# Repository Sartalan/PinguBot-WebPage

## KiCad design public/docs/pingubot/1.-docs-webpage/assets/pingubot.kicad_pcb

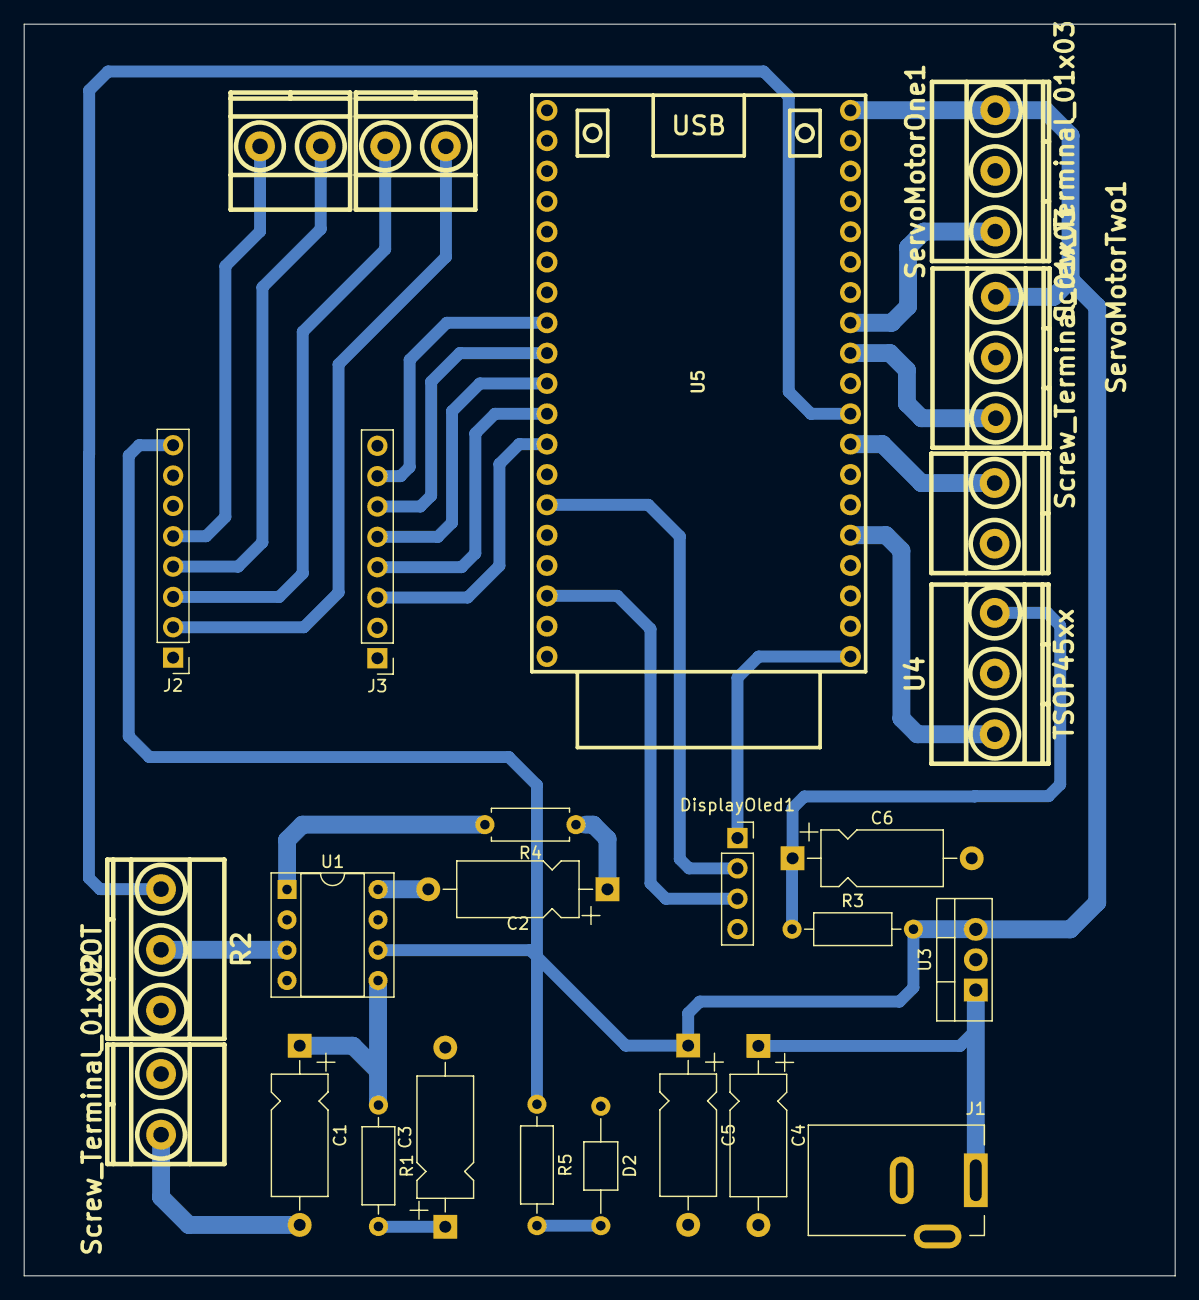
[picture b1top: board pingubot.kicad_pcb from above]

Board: 2 copper layers, 96.3 x 104.8 mm, 26 parts (0 on the bottom side), 29 nets.

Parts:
C1: 220μF; CP_Axial_L10.0mm_D4.5mm_P15.00mm_Horizontal
C2: 10μF; CP_Axial_L10.0mm_D4.5mm_P15.00mm_Horizontal
C3, C6: 0.1yF; CP_Axial_L10.0mm_D4.5mm_P15.00mm_Horizontal
C4, C5: 1μf; CP_Axial_L10.0mm_D4.5mm_P15.00mm_Horizontal
D2: LED; C_Axial_L3.8mm_D2.6mm_P10.00mm_Horizontal
DisplayOled1: Screw_Terminal_01x04; PinSocket_1x04_P2.54mm_Vertical
J1: Jack-DC; BarrelJack_Kycon_KLDX-0202-xC_Horizontal
J2, J3: Conn_01x08_Pin; PinHeader_1x08_P2.54mm_Vertical
Microphone1: Screw_Terminal_01x02; BORNERA2
MotorOne1: Screw_Terminal_01x02; BORNERA2
MotorTwo1: Screw_Terminal_01x02; BORNERA2
R1: 10; R_Axial_DIN0207_L6.3mm_D2.5mm_P10.16mm_Horizontal
R2: POT; BORNERA3
R3: 100; R_Axial_DIN0207_L6.3mm_D2.5mm_P10.16mm_Horizontal
R4: 1,2K; R_Axial_DIN0207_L6.3mm_D2.5mm_P7.62mm_Horizontal
R5: 220; R_Axial_DIN0207_L6.3mm_D2.5mm_P10.16mm_Horizontal
ServoMotorOne1: Screw_Terminal_01x03; BORNERA3
ServoMotorTwo1: Screw_Terminal_01x03; BORNERA3
Speaker1: Screw_Terminal_01x02; BORNERA2
U1: LM386; DIP-8_W7.62mm_Socket
U3: LM7805_TO220; TO-220-3_Vertical
U4: TSOP45xx; BORNERA3
U5: ESP32_DEVKITC

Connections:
3.3V: DisplayOled1.1, U5.1 (3V3)
5V: C5.1, J2.8, R3.2, R5.1, ServoMotorOne1.3, ServoMotorTwo1.3, U1.6 (V+), U3.3 (VO), U5.19 (5V)
GND: C3.2, C4.2, C5.2, C6.2, D2.1 (K), DisplayOled1.4, J1.2, J2.1, J2.6, J3.1, Microphone1.1, R2.3, ServoMotorOne1.2, ServoMotorTwo1.2, Speaker1.1, U1.2 (-), U1.4 (GND), U3.2 (GND), U4.2 (GND), U5.38 (GND)
IR_DATA: U4.1 (OUT), U5.5 (IO34)
MA1: J3.6, U5.28 (IO17)
MA2: J3.7, U5.27 (IO16)
MB1: J3.4, U5.30 (IO18)
MB2: J3.3, U5.31 (IO19)
MO1: J2.5, MotorOne1.2
MO2: J2.4, MotorOne1.1
MO3: J2.3, MotorTwo1.2
MO4: J2.2, MotorTwo1.1
Microphone ADC: Microphone1.2, U5.8 (IO33)
unnamed: C1.1, R1.1, U1.5
unnamed: C2.1, R4.1
unnamed: C2.2, U1.8 (GAIN)
unnamed: C3.1, R1.2
unnamed: D2.2 (A), R5.2
unnamed: R4.2, U1.1 (GAIN)
unnamed: C1.2, Speaker1.2
unnamed: R2.2, U1.3 (+)
unnamed: C6.1, R3.1, U4.3 (Vs)
SCL_DISPLAY: DisplayOled1.3, U5.36 (IO22)
SDA_DISPLAY: DisplayOled1.2, U5.33 (IO21)
STBY: J3.5, U5.29 (IO5)
S_Motor_OUT_1: ServoMotorTwo1.1, U5.11 (IO27)
S_Motor_OUT_2: ServoMotorOne1.1, U5.12 (IO14)
Speaker DAC: R2.1, U5.9 (IO25)
VIN: C4.1, J1.1, U3.1 (VI)

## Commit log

2025-02-12 Initial commit from Astro
2025-02-13 First Viewport Estructure Finished.
2025-02-20 Home Component Improvement
2025-02-20 Nav Improvement
2025-02-20 Footer Improvement
2025-02-20 Nav Icons Added | Nav Component Improved
2025-02-21 Responsive Nav
2025-02-21 Refactor almost all the code from the Nav | pls
2025-02-21 Code Refactored yay
2025-03-01 KiCanvas Api Added
2025-03-01 Nav | Bug Fixed
2025-03-01 View Transition Added
2025-03-02 Dinamic Path's Added
2025-05-05 Preact Integration
2025-05-05 Bugs Fixed (and get request in project!
2025-05-14 Style Improvement yay!
2025-05-28 Text Improvement yayyyy
2025-06-19 Design Improvement (I'm bored aaa)
2025-06-26 Docs Webpage added
2025-06-30 Code Refactored without pages rendered by client-side
2025-06-30 Bug fixed
2025-06-30 Model fixed
2025-06-30 KiCad fixed
2025-06-30 All bugs are fixed
2025-06-30 Model [...] fixed (?
2025-06-30 Model [...] not fixed | I don't know how to fix the bug yet
2025-07-01 Blog Newsletter | v0.1
2025-07-02 Blog | Sketch Added | v0.2
2025-07-03 Blog | Dick Sketch Deleted XD (My friend drew it) | v0.3
2025-07-03 Blog | Details | v0.3.5
2025-11-18 Test (?
2025-11-18 Test from Sarti User
2025-11-22 Blog | MVP | v0.4
2025-11-22 Blog | Details | v0.4.1
2025-11-22 Blog | Details | v0.4.2
